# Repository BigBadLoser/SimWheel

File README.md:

# SimWheel

Source files for my Ferrari SF90 F1 wheel. Uses a PGA2350 as the main processor, 
also uses an Adafruit USB hub of some sort, allows one cable for output even with the VoCore usb screen installed :)

###TODO:
- Fix HAT switch wiring.
- Move upper led_din to a GPIO pin that supports PIO (oops)
- add connectors for the rear 2 push buttons that i forgot

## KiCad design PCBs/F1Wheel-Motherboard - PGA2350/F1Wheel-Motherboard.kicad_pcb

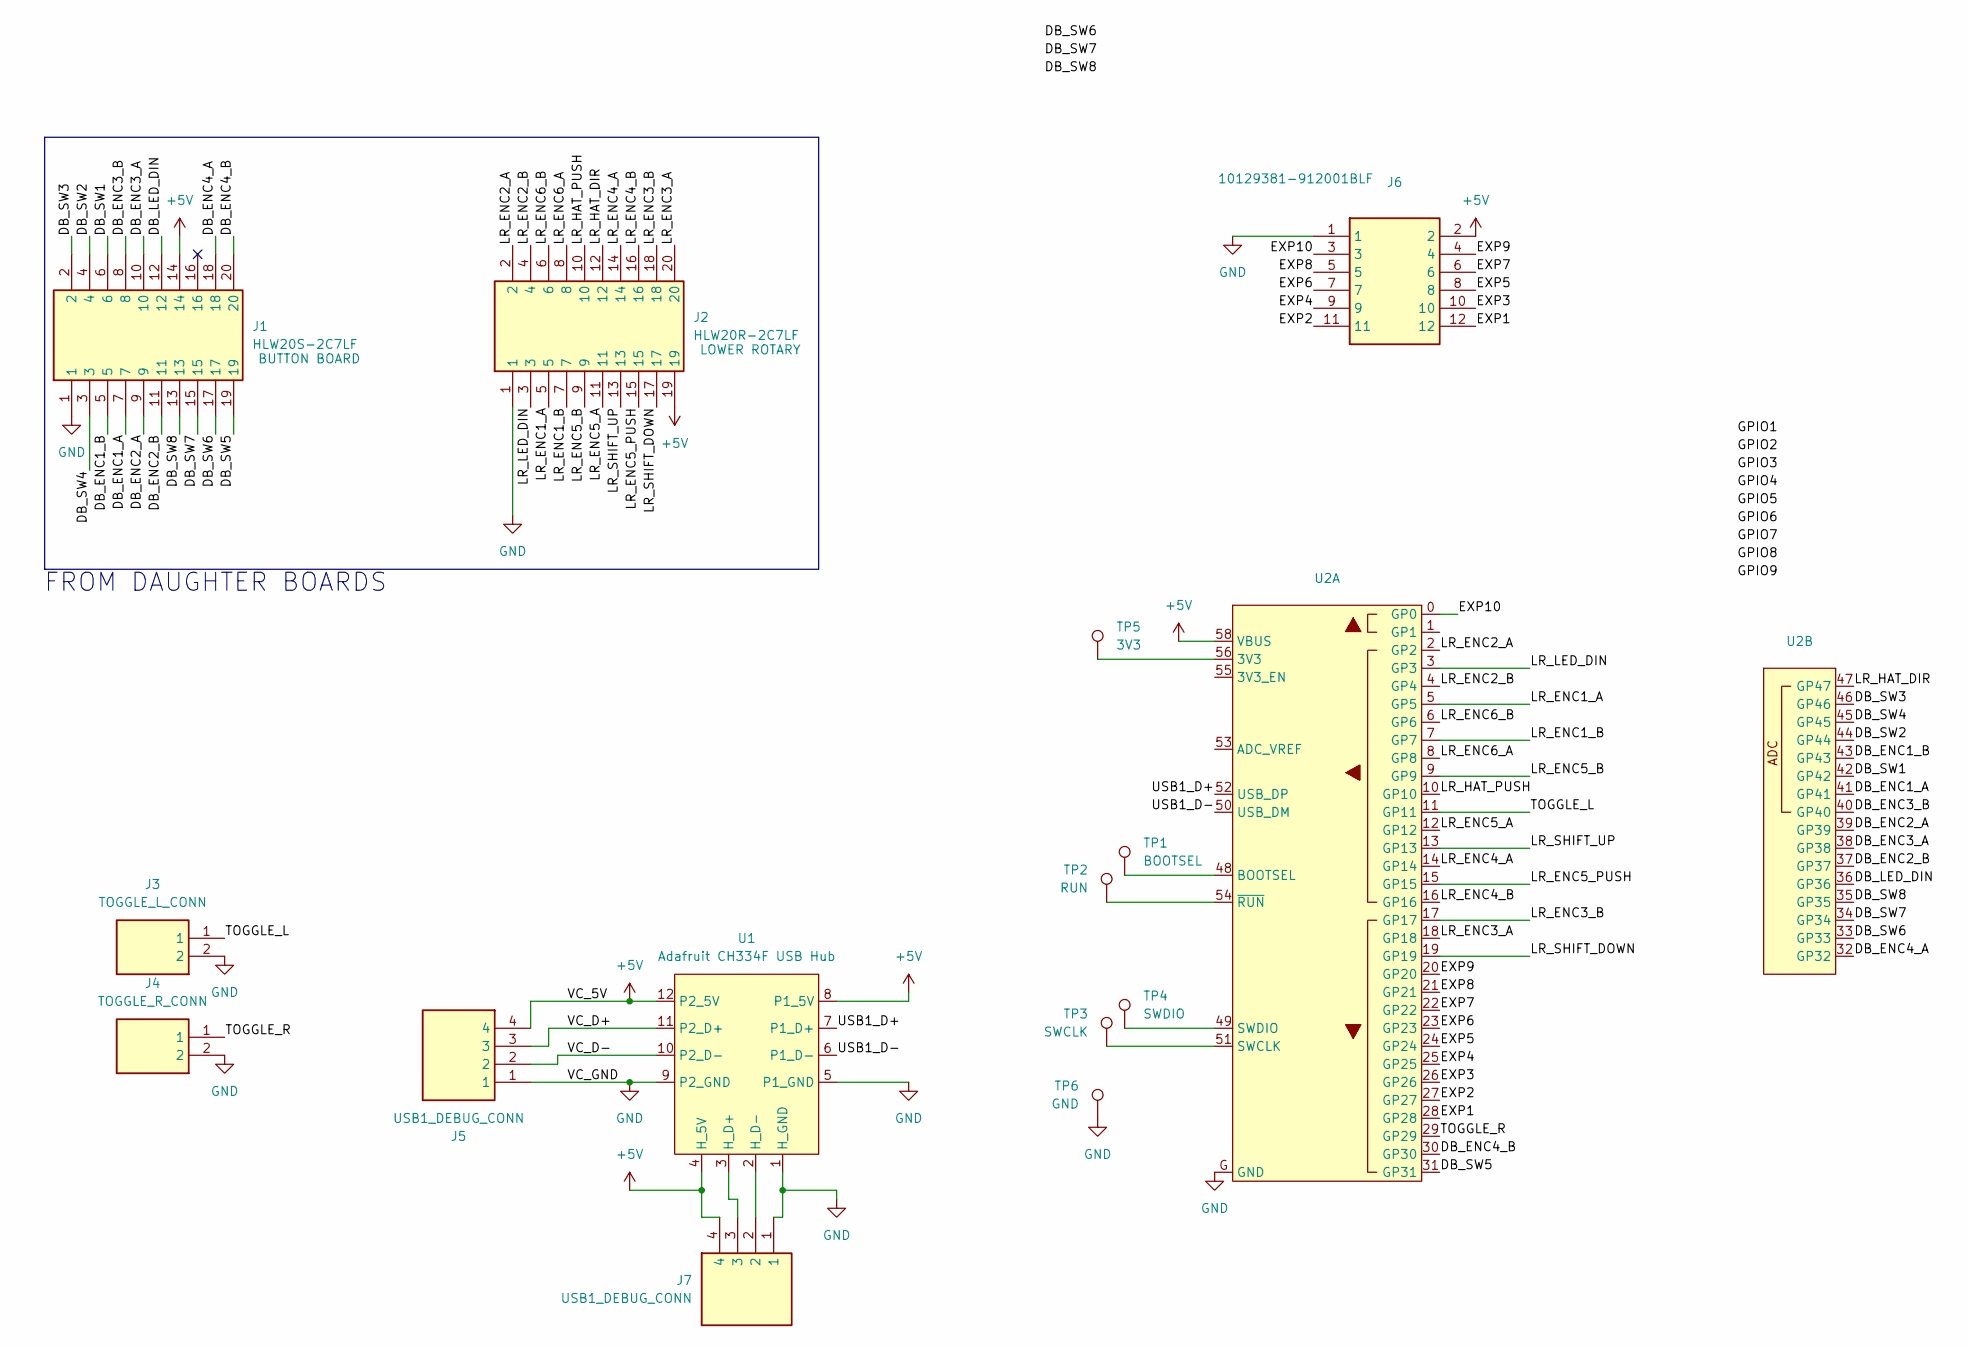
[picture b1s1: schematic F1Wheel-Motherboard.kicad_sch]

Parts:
J1: HLW20S-2C7LF; AMPHENOL_HLW20S2C7LF; Mouser Part Number 649-HLW16R-2C7LF
J2: HLW20R-2C7LF; AMPHENOL_HLW20R-2C7LF; Mouser Part Number 649-HLW16R-2C7LF
J3: TOGGLE_L_CONN; B02BPASKLFSN; Mouser Part Number 306-B02BPASKLFSN
J4: TOGGLE_R_CONN; B02BPASKLFSN; Mouser Part Number 306-B02BPASKLFSN
J5, J7: USB1_DEBUG_CONN; B04BPASKLFSN; Mouser Part Number 306-B04BPASKLFSN
J6: 10129381-912001BLF; HDRV12W67P254_2X6_1524X483X858P; Manufacturer_Part_Number 10129381-912001BLF
TP1: BOOTSEL; TestPoint_Keystone_5005-5009_Compact
TP2: RUN; TestPoint_Keystone_5005-5009_Compact
TP3: SWCLK; TestPoint_Keystone_5005-5009_Compact
TP4: SWDIO; TestPoint_Keystone_5005-5009_Compact
TP5: 3V3; TestPoint_Keystone_5005-5009_Compact
TP6: GND; TestPoint_Keystone_5005-5009_Compact
U1: Adafruit CH334F USB Hub; Adafruit_CH334F_2Port
U2: PGA2350_ALT

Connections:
+5V: J1.14, J2.19, J5.4, J6.2, J7.4, U1.4 (H_5V), U1.8 (P1_5V), U1.12 (P2_5V), U2.58 (VBUS)
/DB_ENC1_A: J1.7, U2.41 (GP41)
/DB_ENC1_B: J1.5, U2.43 (GP43)
/DB_ENC2_A: J1.9, U2.39 (GP39)
/DB_ENC2_B: J1.11, U2.37 (GP37)
/DB_ENC3_A: J1.10, U2.38 (GP38)
/DB_ENC3_B: J1.8, U2.40 (GP40)
/DB_ENC4_A: J1.18, U2.32 (GP32)
/DB_ENC4_B: J1.20, U2.30 (GP30)
/DB_LED_DIN: J1.12, U2.36 (GP36)
/DB_SW1: J1.6, U2.42 (GP42)
/DB_SW2: J1.4, U2.44 (GP44)
/DB_SW3: J1.2, U2.46 (GP46)
/DB_SW4: J1.3, U2.45 (GP45)
/DB_SW5: J1.19, U2.31 (GP31)
/DB_SW6: J1.17, U2.33 (GP33)
/DB_SW7: J1.15, U2.34 (GP34)
/DB_SW8: J1.13, U2.35 (GP35)
/EXP1: J6.12, U2.28 (GP28)
/EXP2: J6.11, U2.27 (GP27)
/EXP3: J6.10, U2.26 (GP26)
/EXP4: J6.9, U2.25 (GP25)
/EXP5: J6.8, U2.24 (GP24)
/EXP6: J6.7, U2.23 (GP23)
/EXP7: J6.6, U2.22 (GP22)
/EXP8: J6.5, U2.21 (GP21)
/EXP9: J6.4, U2.20 (GP20)
/EXP10: J6.3, U2.0 (GP0)
/LR_ENC1_A: J2.5, U2.5 (GP5)
/LR_ENC1_B: J2.7, U2.7 (GP7)
/LR_ENC2_A: J2.2, U2.2 (GP2)
/LR_ENC2_B: J2.4, U2.4 (GP4)
/LR_ENC3_A: J2.20, U2.18 (GP18)
/LR_ENC3_B: J2.18, U2.17 (GP17)
/LR_ENC4_A: J2.14, U2.14 (GP14)
/LR_ENC4_B: J2.16, U2.16 (GP16)
/LR_ENC5_A: J2.11, U2.12 (GP12)
/LR_ENC5_B: J2.9, U2.9 (GP9)
/LR_ENC5_PUSH: J2.15, U2.15 (GP15)
/LR_ENC6_A: J2.8, U2.8 (GP8)
/LR_ENC6_B: J2.6, U2.6 (GP6)
/LR_HAT_DIR: J2.12, U2.47 (GP47)
/LR_HAT_PUSH: J2.10, U2.10 (GP10)
/LR_LED_DIN: J2.3, U2.3 (GP3)
/LR_SHIFT_DOWN: J2.17, U2.19 (GP19)
/LR_SHIFT_UP: J2.13, U2.13 (GP13)
/TOGGLE_L: J3.1, U2.11 (GP11)
/TOGGLE_R: J4.1, U2.29 (GP29)
/USB1_D+: U1.7 (P1_D+), U2.52 (USB_DP)
/USB1_D-: U1.6 (P1_D-), U2.50 (USB_DM)
/VC_D+: J5.3, U1.11 (P2_D+)
/VC_D-: J5.2, U1.10 (P2_D-)
GND: J1.1, J2.1, J3.2, J4.2, J5.1, J6.1, J7.1, TP6.1, U1.1 (H_GND), U1.5 (P1_GND), U1.9 (P2_GND), U2.G (GND)
unnamed: J7.3, U1.3 (H_D+)
unnamed: J7.2, U1.2 (H_D-)
unnamed: TP5.1, U2.56 (3V3)
unnamed: TP1.1, U2.48 (BOOTSEL)
unnamed: TP3.1, U2.51 (SWCLK)
unnamed: TP4.1, U2.49 (SWDIO)
unnamed: TP2.1, U2.54 (~RUN)

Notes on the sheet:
FROM DAUGHTER BOARDS

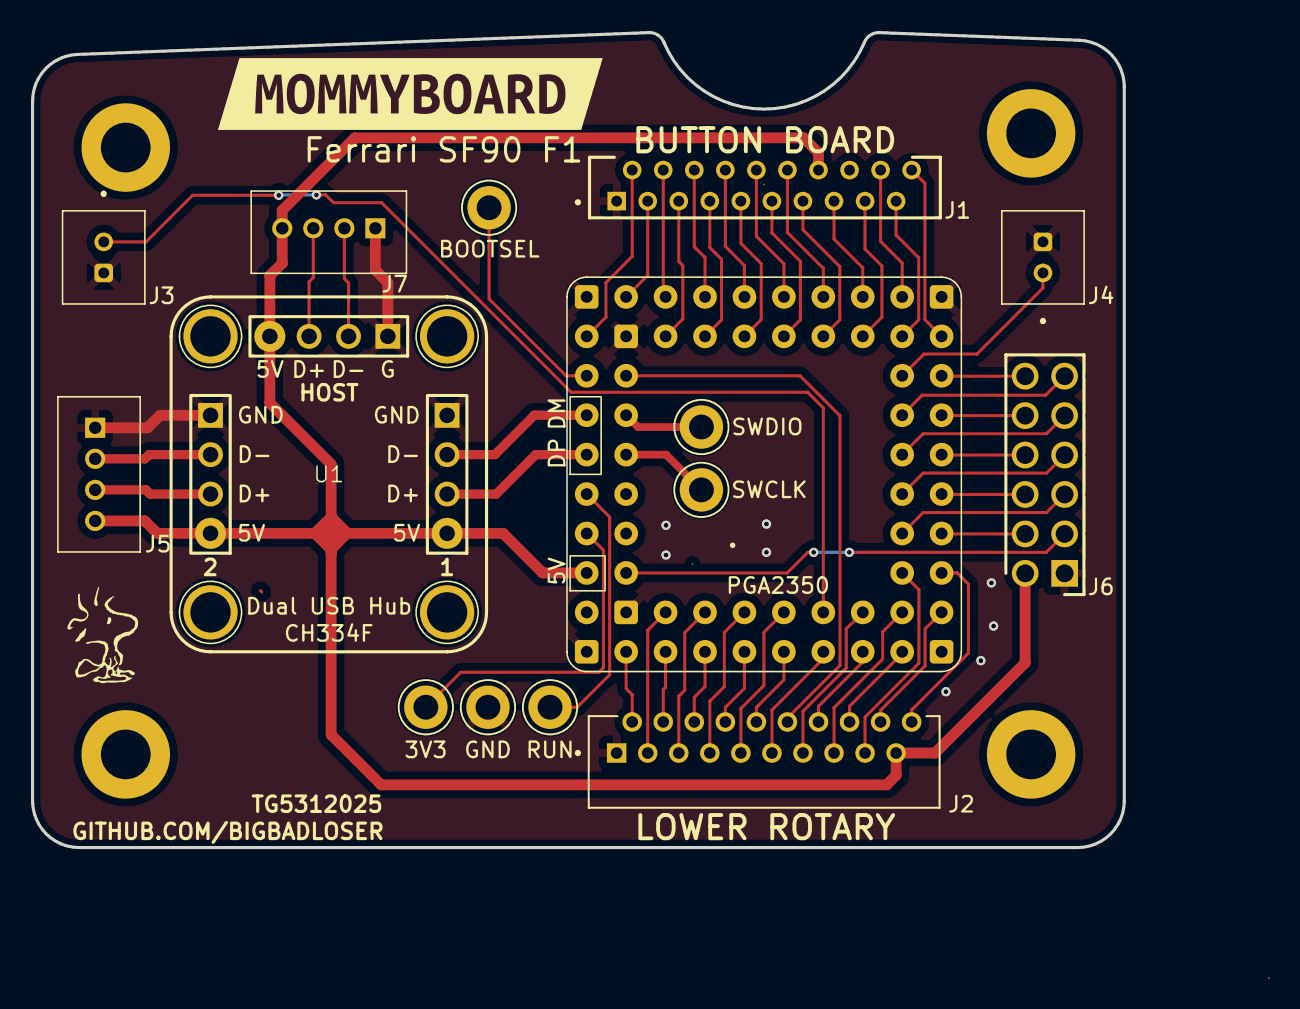
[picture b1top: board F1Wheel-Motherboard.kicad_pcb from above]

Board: 2 copper layers, 70.3 x 52.5 mm, 16 parts (0 on the bottom side), 60 nets.

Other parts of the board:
kibuzzard-683A7EFC: G***; kibuzzard-683A7EFC

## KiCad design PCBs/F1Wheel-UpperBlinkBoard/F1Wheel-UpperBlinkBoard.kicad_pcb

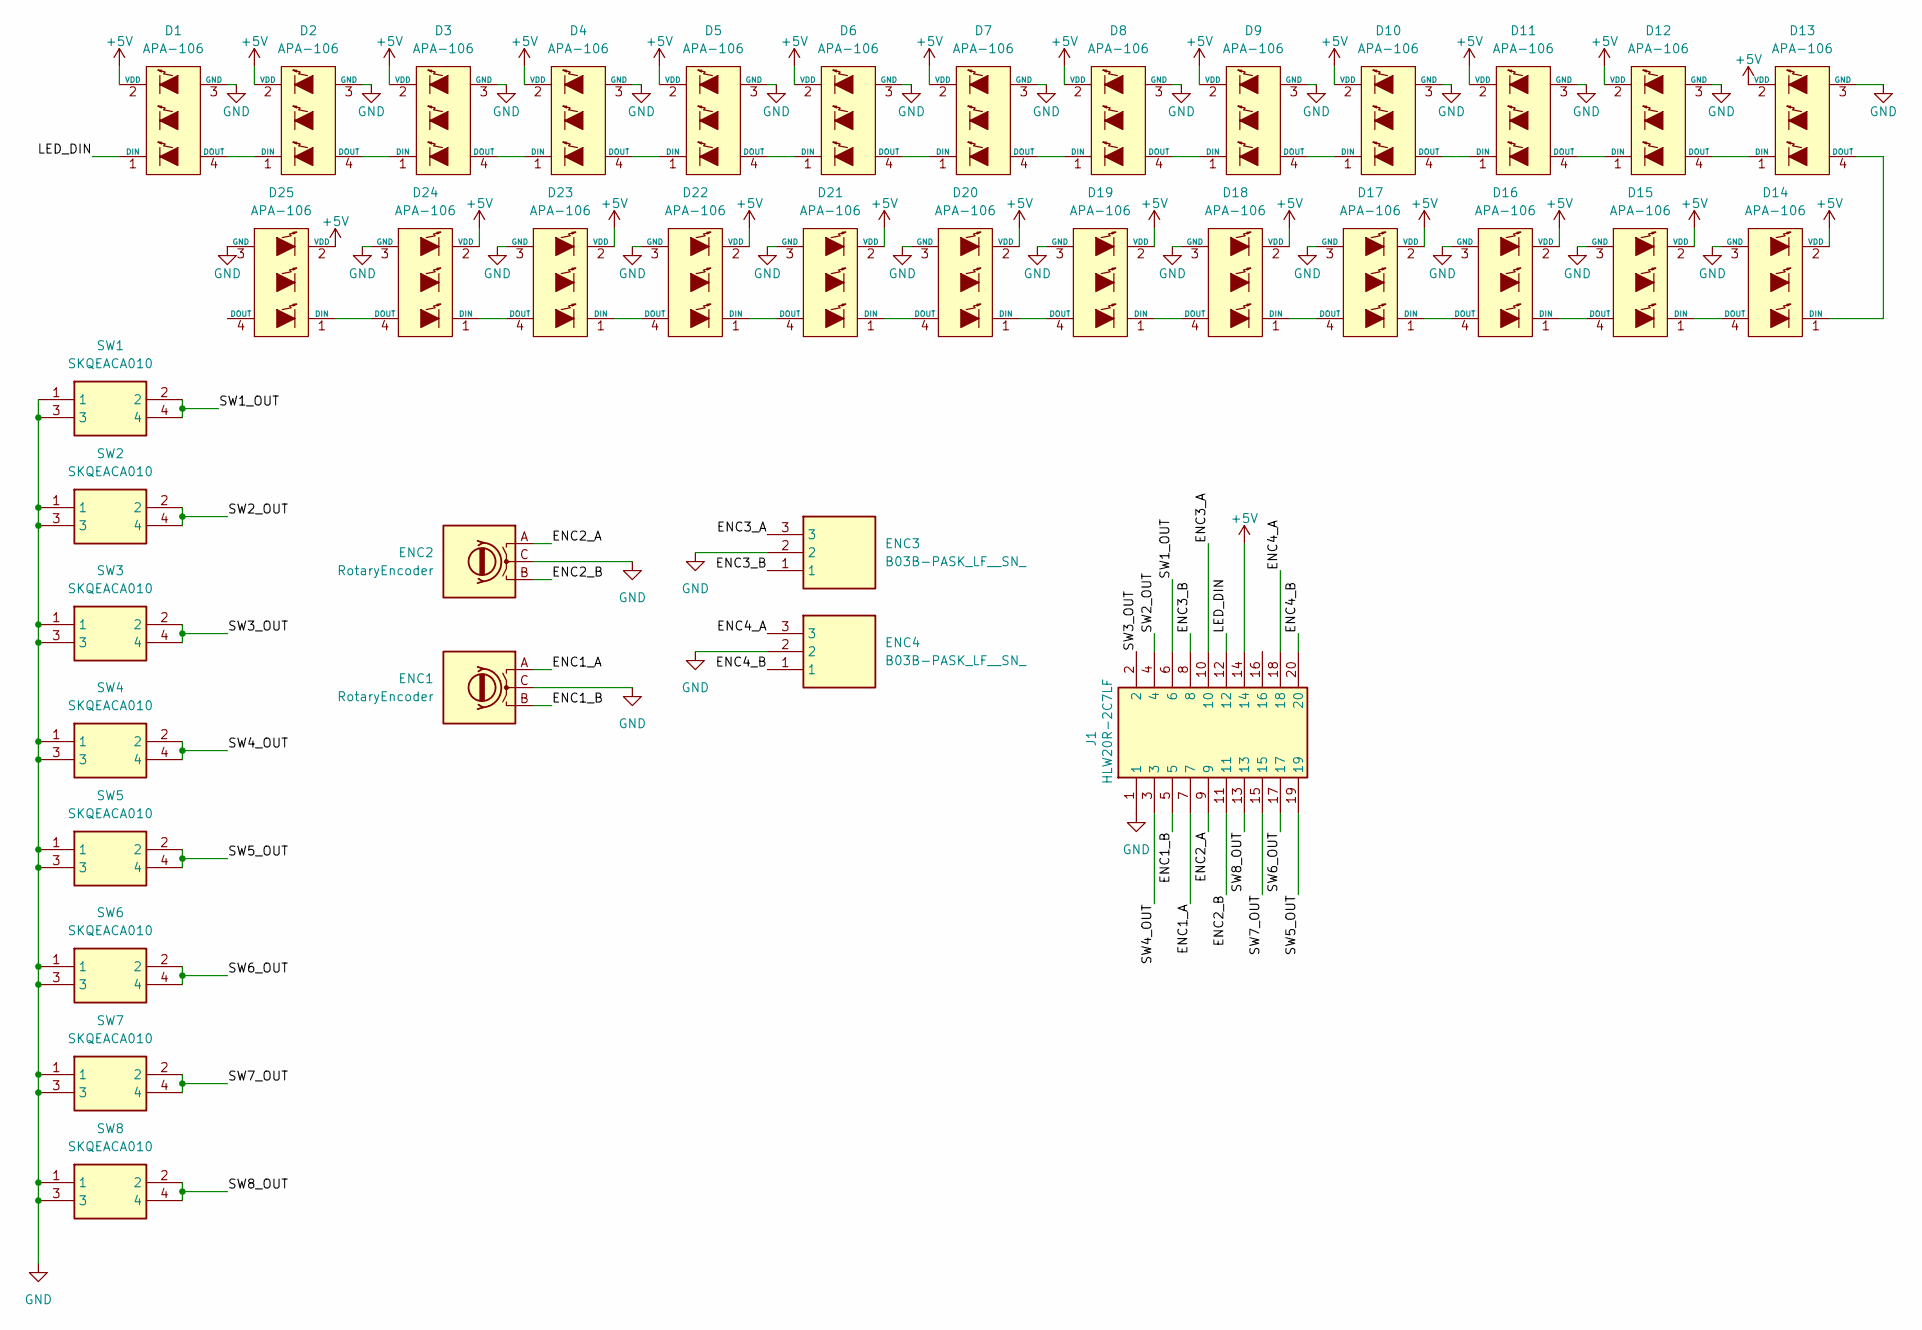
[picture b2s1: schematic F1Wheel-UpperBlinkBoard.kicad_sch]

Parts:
D1, D2, D3, D4, D5, D6, D7, D8, D9, D10, D11, D12, D13, D14, D15, D16, D17, D18, D19, D20, D21, D22, D23, D24, D25: APA-106; APA-106-F5
ENC1, ENC2: RotaryEncoder; 288T Encoder
ENC3, ENC4: B03B-PASK_LF__SN_; B03BPASKLFSN; Mouser Part Number 306-B03BPASKLFSN
J1: HLW20R-2C7LF; AMPHENOL_HLW20R-2C7LF; Mouser Part Number 649-HLW16R-2C7LF
SW1, SW2, SW3, SW4, SW5, SW6, SW7, SW8: SKQEACA010; Mouser Part Number 688-SKQEAC

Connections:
+5V: D1.2 (VDD), D2.2 (VDD), D3.2 (VDD), D4.2 (VDD), D5.2 (VDD), D6.2 (VDD), D7.2 (VDD), D8.2 (VDD), D9.2 (VDD), D10.2 (VDD), D11.2 (VDD), D12.2 (VDD), D13.2 (VDD), D14.2 (VDD), D15.2 (VDD), D16.2 (VDD), D17.2 (VDD), D18.2 (VDD), D19.2 (VDD), D20.2 (VDD), D21.2 (VDD), D22.2 (VDD), D23.2 (VDD), D24.2 (VDD), D25.2 (VDD), J1.14
/ENC1_A: ENC1.A, J1.7
/ENC1_B: ENC1.B, J1.5
/ENC2_A: ENC2.A, J1.9
/ENC2_B: ENC2.B, J1.11
/ENC3_A: ENC3.3, J1.10
/ENC3_B: ENC3.1, J1.8
/ENC4_A: ENC4.3, J1.18
/ENC4_B: ENC4.1, J1.20
/LED_DIN: D1.1 (DIN), J1.12
/SW1_OUT: J1.6, SW1.2, SW1.4
/SW2_OUT: J1.4, SW2.2, SW2.4
/SW3_OUT: J1.2, SW3.2, SW3.4
/SW4_OUT: J1.3, SW4.2, SW4.4
/SW5_OUT: J1.19, SW5.2, SW5.4
/SW6_OUT: J1.17, SW6.2, SW6.4
/SW7_OUT: J1.15, SW7.2, SW7.4
/SW8_OUT: J1.13, SW8.2, SW8.4
GND: D1.3 (GND), D2.3 (GND), D3.3 (GND), D4.3 (GND), D5.3 (GND), D6.3 (GND), D7.3 (GND), D8.3 (GND), D9.3 (GND), D10.3 (GND), D11.3 (GND), D12.3 (GND), D13.3 (GND), D14.3 (GND), D15.3 (GND), D16.3 (GND), D17.3 (GND), D18.3 (GND), D19.3 (GND), D20.3 (GND), D21.3 (GND), D22.3 (GND), D23.3 (GND), D24.3 (GND), D25.3 (GND), ENC1.C, ENC2.C, ENC3.2, ENC4.2, J1.1, SW1.1, SW1.3, SW2.1, SW2.3, SW3.1, SW3.3, SW4.1, SW4.3, SW5.1, SW5.3, SW6.1, SW6.3, SW7.1, SW7.3, SW8.1, SW8.3
unnamed: D1.4 (DOUT), D2.1 (DIN)
unnamed: D2.4 (DOUT), D3.1 (DIN)
unnamed: D3.4 (DOUT), D4.1 (DIN)
unnamed: D4.4 (DOUT), D5.1 (DIN)
unnamed: D5.4 (DOUT), D6.1 (DIN)
unnamed: D6.4 (DOUT), D7.1 (DIN)
unnamed: D7.4 (DOUT), D8.1 (DIN)
unnamed: D8.4 (DOUT), D9.1 (DIN)
unnamed: D9.4 (DOUT), D10.1 (DIN)
unnamed: D10.4 (DOUT), D11.1 (DIN)
unnamed: D11.4 (DOUT), D12.1 (DIN)
unnamed: D12.4 (DOUT), D13.1 (DIN)
unnamed: D13.4 (DOUT), D14.1 (DIN)
unnamed: D14.4 (DOUT), D15.1 (DIN)
unnamed: D15.4 (DOUT), D16.1 (DIN)
unnamed: D16.4 (DOUT), D17.1 (DIN)
unnamed: D17.4 (DOUT), D18.1 (DIN)
unnamed: D18.4 (DOUT), D19.1 (DIN)
unnamed: D19.4 (DOUT), D20.1 (DIN)
unnamed: D20.4 (DOUT), D21.1 (DIN)
unnamed: D21.4 (DOUT), D22.1 (DIN)
unnamed: D22.4 (DOUT), D23.1 (DIN)
unnamed: D23.4 (DOUT), D24.1 (DIN)
unnamed: D24.4 (DOUT), D25.1 (DIN)

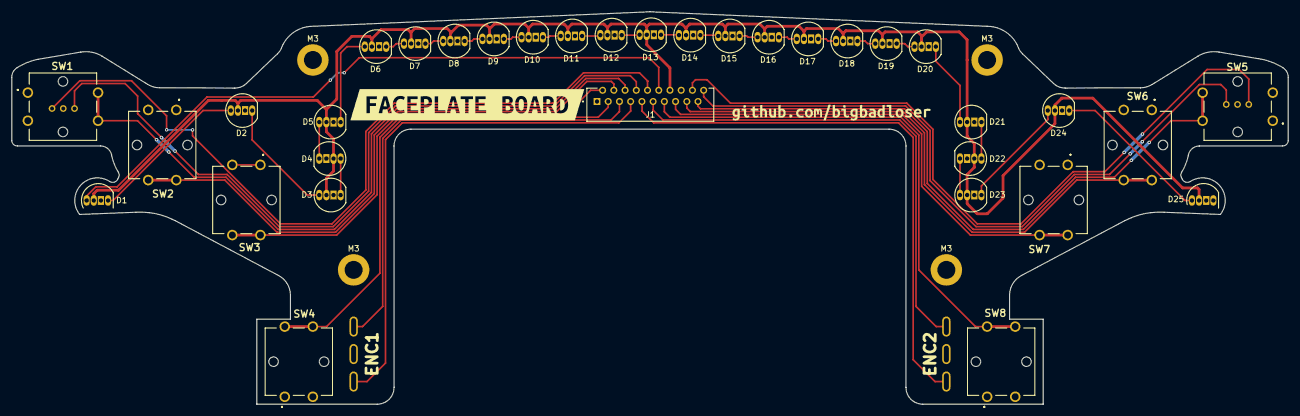
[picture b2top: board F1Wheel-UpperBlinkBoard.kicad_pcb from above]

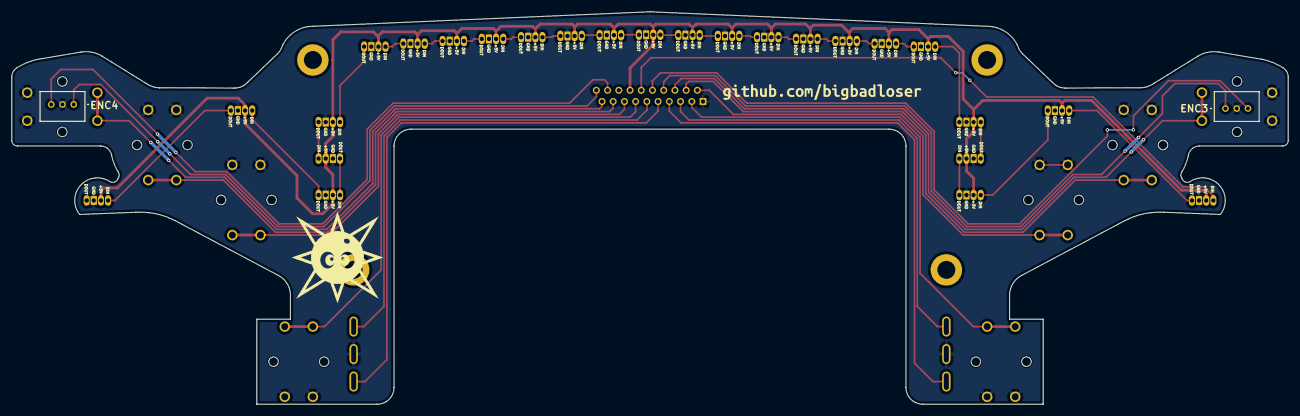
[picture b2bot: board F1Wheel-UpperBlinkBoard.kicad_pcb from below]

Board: 2 copper layers, 227.4 x 69.9 mm, 45 parts (3 on the bottom side), 43 nets.

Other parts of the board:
M3, M3#2, M3#3, M3#4: MountingHole_3.2mm_M3_DIN965_Pad
kibuzzard-683245A1, kibuzzard-683245A1#2: G***; kibuzzard-683245A1
kibuzzard-683248CA: G***; kibuzzard-683248CA

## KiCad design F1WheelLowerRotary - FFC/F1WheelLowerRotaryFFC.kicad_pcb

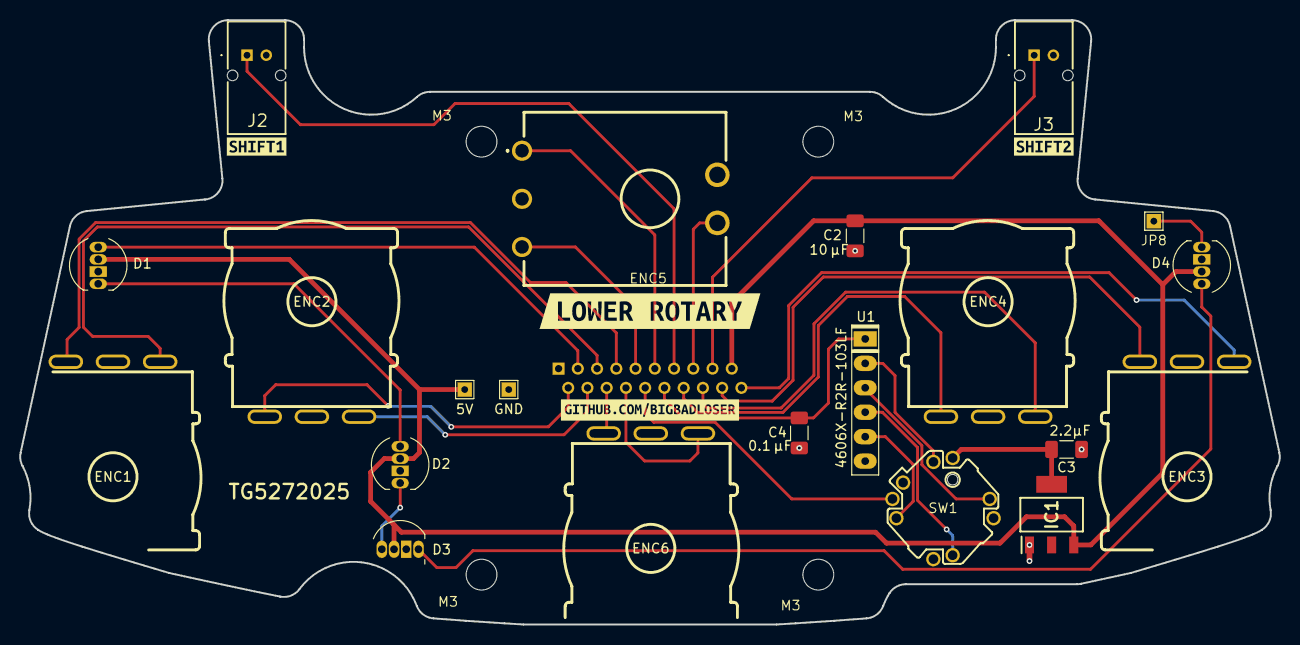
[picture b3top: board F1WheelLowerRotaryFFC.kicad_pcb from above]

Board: 2 copper layers, 130.9 x 62.8 mm, 30 parts (1 on the bottom side), 29 nets.

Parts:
5V: 5V; TestPoint_THTPad_1.5x1.5mm_Drill0.7mm
C2: 10 µF; C_1206_3216Metric_Pad1.33x1.80mm_HandSolder
C3: 2.2µF; C_1206_3216Metric_Pad1.33x1.80mm_HandSolder
C4: 0.1 µF; C_1206_3216Metric_Pad1.33x1.80mm_HandSolder
D1, D2, D3, D4: APA-106; LED_D5.0mm-APA106
ENC1, ENC2, ENC3, ENC4, ENC6: RotaryEncoder; 288T Encoder
ENC5: 288V232R161B2
GND: GND; TestPoint_THTPad_1.5x1.5mm_Drill0.7mm
IC1: TLV76133DCYR; SOT230P700X180-4N
J2: SW_SHIFT1; JST_S02B-PASK-2
J3: SW_SHIFT2; JST_S02B-PASK-2
J14: HLW20R-2C7LF; AMPHENOL_HLW20R-2C7LF
JP8: DOUT; TestPoint_THTPad_1.5x1.5mm_Drill0.7mm
M3, M3#2, M3#3, M3#4: MountingHole_3.2mm_M3
SW1: RKJXM1015004
U1: 4606X-R2R-103LF; R_Array_SIP6_BigPads
kibuzzard-682F5760: G***; kibuzzard-682F5760
kibuzzard-682F5782: G***; kibuzzard-682F5782
kibuzzard-68364A1D: G***; kibuzzard-68364A1D
kibuzzard-683649BF: G***; kibuzzard-683649BF

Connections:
+3.3V: C3.2, IC1.2 (OUT_1), IC1.4 (OUT_2), SW1.COM
+5V: 5V.1, C2.2, D1.2 (VDD), D2.2 (VDD), D3.2 (VDD), D4.2 (VDD), IC1.3 (IN), J14.19
/HAT_DOWN: SW1.C (DOWN), U1.2 (BIT1)
/HAT_LEFT: SW1.B (LEFT), U1.3 (BIT2)
/HAT_RIGHT: SW1.D (RIGHT), U1.5 (BIT4)
/HAT_UP: SW1.A (UP), U1.4 (BIT3)
/LR_ENC1_A: ENC1.A, J14.5
/LR_ENC1_B: ENC1.B, J14.7
/LR_ENC2_A: ENC2.A, J14.2
/LR_ENC2_B: ENC2.B, J14.4
/LR_ENC3_A: ENC3.A, J14.20
/LR_ENC3_B: ENC3.B, J14.18
/LR_ENC4_A: ENC4.A, J14.14
/LR_ENC4_B: ENC4.B, J14.16
/LR_ENC5_A: ENC5.A1, J14.11
/LR_ENC5_B: ENC5.B1, J14.9
/LR_ENC5_PUSH: ENC5.S2, J14.15
/LR_ENC6_A: ENC6.A, J14.8
/LR_ENC6_B: ENC6.B, J14.6
/LR_HAT_DIR: C4.2, J14.12, U1.1 (OUT)
/LR_HAT_PUSH: J14.10, SW1.PUSH
/LR_LED_DIN: D1.1 (DIN), J14.3
/LR_SHIFT_DOWN: J3.1, J14.17
/LR_SHIFT_UP: J2.1, J14.13
GND: C2.1, C3.1, C4.1, D1.3 (GND), D2.3 (GND), D3.3 (GND), D4.3 (GND), ENC1.C, ENC2.C, ENC3.C, ENC4.C, ENC5.C1, ENC5.S1, ENC6.C, GND.1, IC1.1 (GND), J2.2, J3.2, J14.1, U1.6 (RT)
unnamed: D1.4 (DOUT), D2.1 (DIN)
unnamed: D2.4 (DOUT), D3.1 (DIN)
unnamed: D3.4 (DOUT), D4.1 (DIN)
unnamed: D4.4 (DOUT), JP8.1

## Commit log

2025-06-26 added files
2025-06-30 organization changes
2025-06-30 fixed image
2025-06-30 added firmware source code
